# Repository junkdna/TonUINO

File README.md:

# TonUINO
Die DIY Musikbox (nicht nur) für Kinder.

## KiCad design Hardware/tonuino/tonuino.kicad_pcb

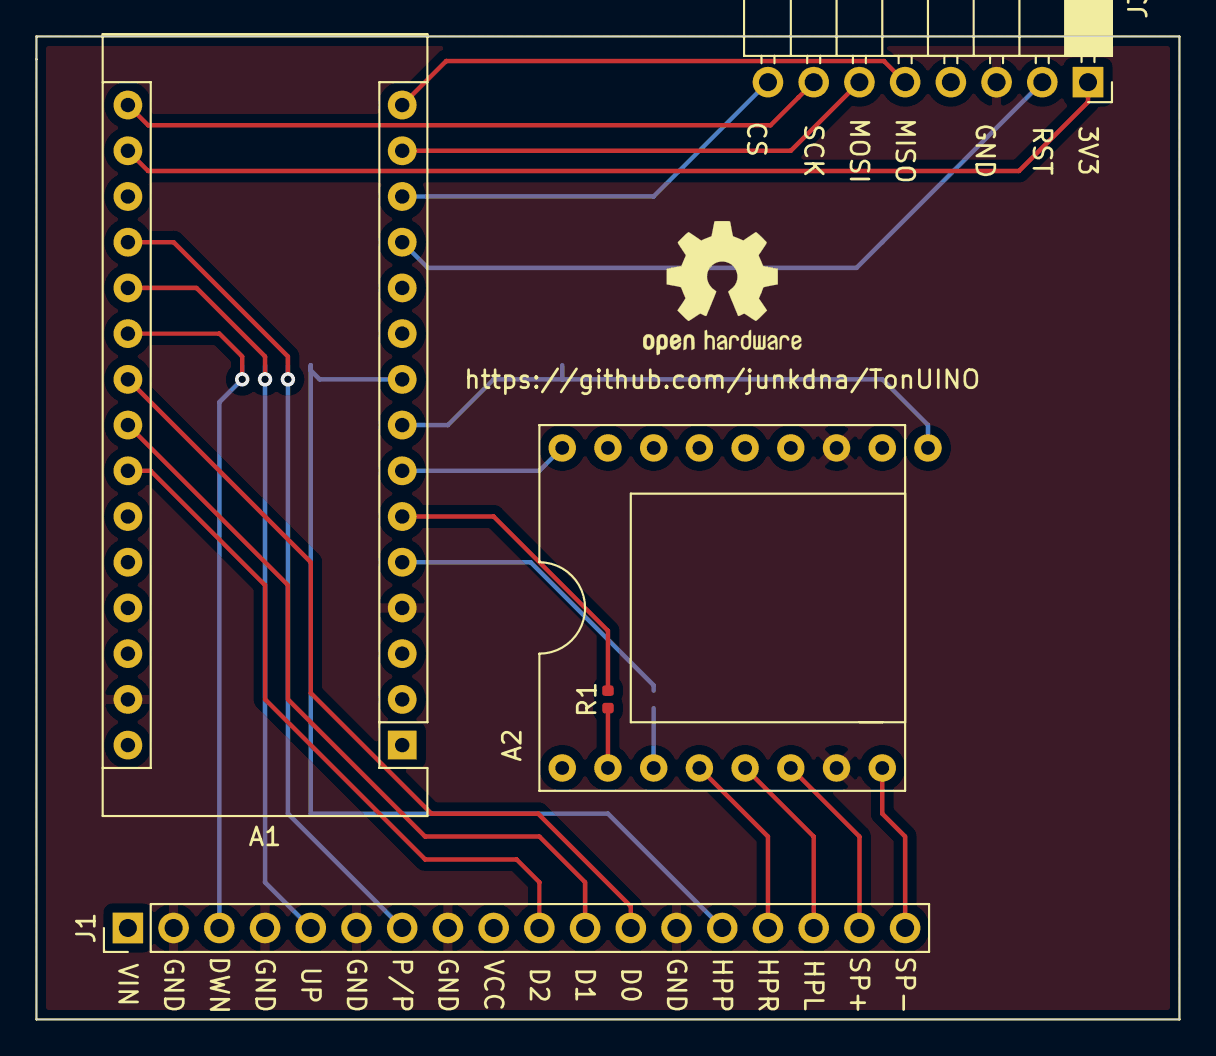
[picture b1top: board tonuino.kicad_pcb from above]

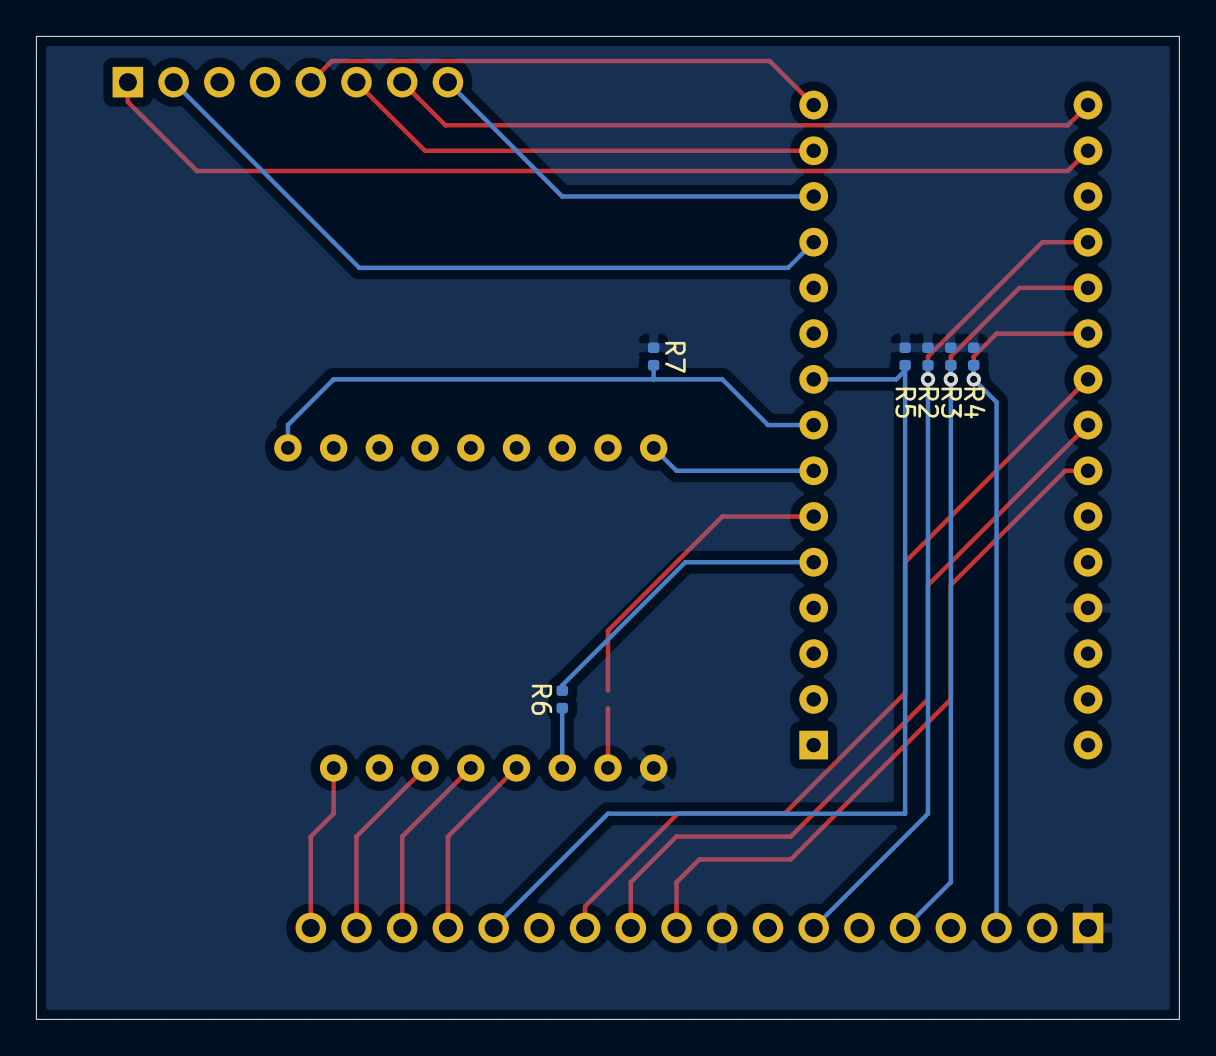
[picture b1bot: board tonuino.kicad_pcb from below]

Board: 2 copper layers, 63.5 x 54.6 mm, 11 parts (6 on the bottom side), 25 nets.

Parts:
A1: Arduino_Nano_v2.x; Arduino_Nano
A2: DFPlayer
J1: Conn_01x18_Female; PinHeader_1x18_P2.54mm_Vertical
J3: Conn_01x08_Female; PinSocket_1x08_P2.54mm_Horizontal
R1: 1k; R_0402_1005Metric
R2, R3, R4, R5, R7: 4k7; R_0402_1005Metric
R6: 0R; R_0402_1005Metric

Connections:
/3V3: A1.17, J3.1
/GND: A1.4, A1.29, A2.7, A2.10, J1.2, J1.4, J1.6, J1.8, J1.13, J3.3
/HEADP_L: A2.5, J1.16
/HEADP_R: A2.4, J1.15
/LED0: A1.22, J1.12
/LED1: A1.23, J1.11
/LED2: A1.24, J1.10
/MISO: A1.15, J3.5
/MOSI: A1.14, J3.6
/RST: A1.12, J3.2
/SCK: A1.16, J3.7
/SPK+: A2.6, J1.17
/SPK-: A2.8, J1.18
/SS: A1.13, J3.8
/VCC: A1.27, A2.1, J1.1, J1.9, R2.1, R3.1, R4.1, R5.1, R7.1
/~DOWN: A1.21, J1.3, R4.2
/~HEADP: A1.9, J1.14, R5.2
/~PAUSE: A1.19, J1.7, R2.2
/~SPK_EN: A1.8, A2.17, R7.2
/~UP: A1.20, J1.5, R3.2
unnamed: A1.5, R6.2
unnamed: A1.6, R1.2
unnamed: A1.7, A2.16
unnamed: A2.2, R1.1
unnamed: A2.3, R6.1

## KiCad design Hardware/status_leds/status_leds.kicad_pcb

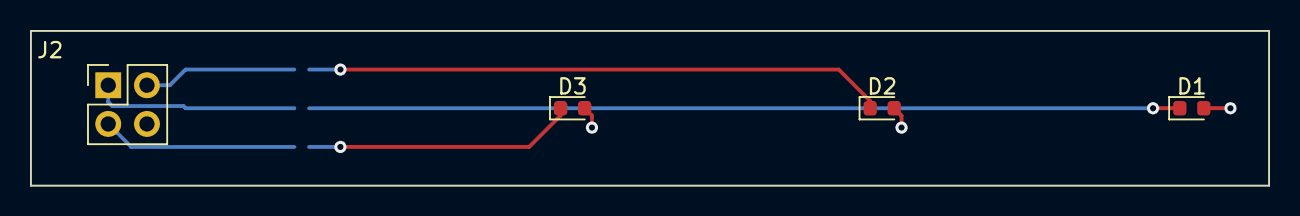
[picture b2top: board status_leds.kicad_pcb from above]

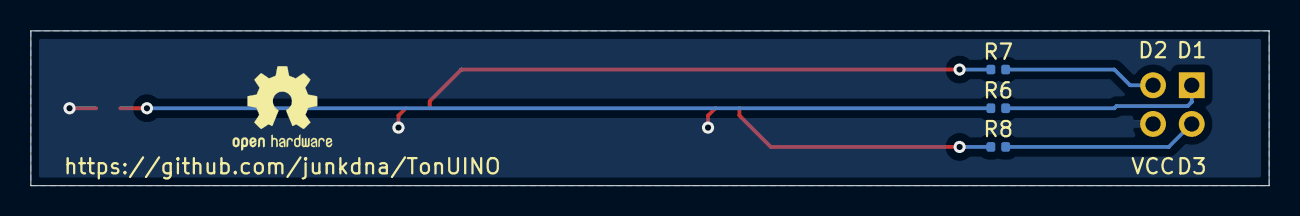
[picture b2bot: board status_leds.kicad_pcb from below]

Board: 2 copper layers, 81.3 x 10.2 mm, 7 parts (3 on the bottom side), 7 nets.

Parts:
D1, D2, D3: LED; LED_0603_1608Metric
J2: Conn_01x04_Female; PinHeader_2x02_P2.54mm_Vertical
R6, R7, R8: 150R; R_0402_1005Metric

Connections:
unnamed: D1.1, R6.1
unnamed: D1.2, D2.2, D3.2, J2.4
unnamed: D2.1, R7.1
unnamed: D3.1, R8.1
unnamed: J2.1, R6.2
unnamed: J2.2, R7.2
unnamed: J2.3, R8.2

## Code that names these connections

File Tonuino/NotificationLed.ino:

/*
 * SPDX-License-Identifier: GPL-3.0-only
 * Copyright 2020 Tillmann Heidsieck <theidsieck@leenox.de>
 */
#include "notification_led.h"

void NotificationLED_3LEDs::loop() {
    uint32_t delta;

    delta = millis() - ms;
    idx %= 3;

    switch (state) {
        case LED_STATE_IDLE:
            if (delta >= 500) {
                digitalWrite(led_pins[idx], 1);
                idx = (idx + 1) % 3;
                digitalWrite(led_pins[idx], 0);
                ms = millis();
            }
            break;
        case LED_STATE_PLAY:
            break;
        case LED_STATE_PAUSE:
            if (delta >= 500) {
                digitalWrite(led_pins[1], idx);
                idx = !idx;
                ms = millis();
            }
            break;
        case LED_STATE_MENU:
            break;
        case LED_STATE_ERROR:
            break;
    }
}

void NotificationLED_3LEDs::update_state(notification_led_state _state) {
    state = _state;
    idx = 0;
    ms = 0;

    /* reset LEDs to off */
    digitalWrite(led_pins[0], 1);
    digitalWrite(led_pins[1], 1);
    digitalWrite(led_pins[2], 1);

    switch (state) {
        case LED_STATE_IDLE:
            digitalWrite(led_pins[0], 0);
            digitalWrite(led_pins[1], 0);
            digitalWrite(led_pins[2], 0);
            break;
        case LED_STATE_PLAY:
            digitalWrite(led_pins[1], 0);
            break;
        case LED_STATE_PAUSE:
            break;
        case LED_STATE_MENU:
            digitalWrite(led_pins[2], 0);
            break;
        case LED_STATE_ERROR:
            digitalWrite(led_pins[0], 0);
            break;
    }
}

NotificationLED_3LEDs::NotificationLED_3LEDs(uint8_t led0, uint8_t led1, uint8_t led2) {
    led_pins[0] = led0;
    led_pins[1] = led1;
    led_pins[2] = led2;
    ms = 0;
    idx = 0;

    pinMode(led_pins[0], OUTPUT);
    pinMode(led_pins[1], OUTPUT);
    pinMode(led_pins[2], OUTPUT);
}

NotificationLED::NotificationLED() {
}

NotificationLED::~NotificationLED() {
}
// vim: ts=4 sw=4 et cindent

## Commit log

2019-12-14 adapt to custom tonuino
2019-12-16 tonuino: indent 4 spaces
2019-12-16 add vim swp files to ignore
2019-12-21 split application code into classes and files
2019-12-22 start implementing the functionality in the new structure
2019-12-26 implement menu (for new card) using new structure
2019-12-26 imported 81d15ffc25344f21b33bbc8fe18b588d05613354 from origin/DEV
    implemented the idea for a better random number generator seed from upstream
2019-12-28 clean up Menu state, improve name
2019-12-28 the rfid code is an example not original code, authorship is important
2019-12-28 clean up RFID reader/writer code
2019-12-28 fix typo in chip id generation
2019-12-28 add toggle for different wirings
2019-12-28 some more cleanup, get rid of compiler warnings
2019-12-28 remove play global tracks states
2019-12-28 rfid: coding style
2019-12-28 rfid: calculate trailer block and sector
2019-12-28 state: make things more consistent
2019-12-28 rfid: style
2019-12-28 rfid: fix card write problem
2019-12-28 state: fix crash after new card
2019-12-28 state: print volume on change
2019-12-28 tonuino: remove mp3 notify debug messages
2019-12-28 buttons: use one bitmap for all events not individual ones
2019-12-28 state: add mp3 event handler for idle state
2019-12-28 state: idle(context) sets the volume not only intialises its internal tracking var
2019-12-28 add some comments noting points for improvement
2019-12-28 state: initial mp3 event handler for album state
2019-12-28 state: remove global_* -> yagni
2019-12-28 state: improve tracking of current track/folder
2019-12-28 state: add play advert wrapper
2019-12-28 state: add play random track from folder helper
2019-12-28 state: fix start() helper
2019-12-28 config: only create new chip_id if id integrity check fails
2019-12-28 config: move to dedicated file
2019-12-28 state: extract button action for vol +/-, next/prev in preperation of config or compile option
2019-12-28 state: harmonise the dfplay_event handler functions basic structure
2019-12-28 state: NewCard: restart and reset tag on initialised tag
2019-12-28 state: harmonise comment in handle_card
2019-12-28 state: implement basic behaviour for states
2019-12-28 setting volume from idle constructor does not work
2019-12-28 state: NewCard: fix track number output
2019-12-28 state: NewCard: save track for single mode in extdata[2] instead of 3
2019-12-28 state: start playing according to card mode
2019-12-28 rfid: fix buffer to struct copy
2019-12-28 state: remove remanents
2019-12-28 rfid: go into correct state in case of errors
2019-12-28 state: AudioBook: fix current_track initialisation
2019-12-28 state: implement prev/next using playFolderTrack
2019-12-28 buttons: ignore release after long_press and only count long_press once
2019-12-28 state: prev/next track numbers are one-indexed
2019-12-28 rfid: clean up check()
2019-12-28 state: do some dirty things to get RadioPlay working
2019-12-29 remove binary files from git
2019-12-29 move schematic to dedicated folder
2019-12-29 move helper script to dedicated folder
2019-12-29 make soundfiles reproducible and match numbers to code
2019-12-29 do not commit mp3 or wave files
2019-12-30 state: improve card handle functions, ignore cards on active playback
2019-12-31 remove non-reproducible schematic pdf
2019-12-31 state: ignore cards in all active states
2019-12-31 state: RadioPlay: fix random play
2019-12-31 state: remove deactivated code
2020-01-03 Merlin/hardware (#1)
    hardware: add baseboard for arduino nano and dfplayer
2020-01-03 state: NewCard: set correct card type for admin cards
2020-01-03 state: skipping 10 modes at a time makes no sense
2020-01-03 state: add simple menu and admin cards to enter it
2020-01-04 make: adapt clean rule
2020-01-04 workflow: test: do not force master branch
2020-01-04 add platformio support
    inspired by
    https://github.com/xfjx/TonUINO/pull/55/
    https://github.com/xfjx/TonUINO/pull/47/
2020-01-04 rfid: fix cppcheck warnings
2020-01-04 ignore build artifacts
2020-01-04 state: fix cppcheck warnings
2020-01-04 readme: add badge
2020-01-04 workflow: test: set working directory
2020-01-04 make: add check target to run c++ check
2020-01-04 add github workflow according to
    https://github.com/xfjx/TonUINO/pull/55
2020-01-04 makefile: remove prepare target
2020-01-04 make: integrate tags generation
2020-01-04 make: update according to referenced pull request
    https://github.com/xfjx/TonUINO/pull/55
2020-01-04 make: fix help
2020-01-04 readme: set correct workflow name
2020-01-05 tools: add gcloud speech synth
2020-01-07 hardware: add additional pull-up for spk_en signal
2020-01-07 hardware: update pcbs
2020-01-07 hardware: prepare split
2020-01-08 Tonuino: add copyright notices to all files
2020-01-08 state: coding style
2020-01-08 state: AlbumRandom: make name consistent
2020-01-08 state: volume: use configured volume steps for inc/dec
2020-01-08 state: clean-up previous state on new card
2020-01-08 make: import changes from upstream
    https://github.com/xfjx/TonUINO/pull/55
2020-01-08 state: NewCard: wrap around selection
2020-01-08 readme: update build badge
2020-01-08 state: get folder track count if not set
2020-01-08 make: remove tags on clean
2020-01-08 state: account for double finished events in dfplay event handler
2020-01-08 make: remove some host dependencies
2020-01-08 state: split up TState.ino into one file per state
    This should improve readability and maintainability.
2020-01-08 make: add some dependencies in order to get a rebuild if required
2020-01-08 state: restore paused playback on play/pause in idle mode
2020-01-08 tonuino: implement configuration reset
2020-01-08 state: play a message on leaving a menu via long press auf play/pause
2020-01-08 rfid: bind card to magic not chip_id
2020-01-08 state: make volume/next/prev configurable
2020-01-08 make: install setuptools and wheel right before platformio
2020-01-08 config: set initial minimal volume to valid value
2020-03-21 config: remove chip id
2020-03-21 hardware: tonuino: fix LED pins, A6/7 are ADC only and wont work as outputs
2020-03-21 player: allow reset of state
2020-03-21 state: idle: play welcome, error on first init, error
2020-03-21 state: idle: track error state
2020-03-21 player/state: add interaction through loop
2020-03-21 player: remove advert on volume change
2020-03-21 player: make player more robust
2020-03-21 player/state: fix regressions
2020-03-21 player: implement random queue instead of pure random mode
2020-03-21 player: fix advert
2020-03-21 button: add define to switch on internal pull-ups for buttons
2020-03-21 tools: create soundfiles: fix skipping
2020-03-21 tools: create soundfiles: put advert and mp3 in the correct folders
2020-03-21 state: fix uninitialised value
2020-03-21 tstate: coding style
2020-03-21 player: play advert on vol up/down
2020-03-21 player: random: do some more rounds of shuffle
2020-03-21 player: get and store global track number
2020-03-21 data/tools: add, sort, modify some messages
2020-03-21 init: do more rounds of random initialisation
2020-03-21 new card: delete any time of card
2020-03-21 mod: LockKeys: return state
2020-03-21 RFID: remove debug code, save 10% flash space
2020-03-21 menu: adjust volume as a preview for volume settings
2020-03-21 player: shuffle: do more rounds for better shuffle
2020-03-21 new card: add modificator card creation
2020-03-21 data: soundfiles: fix/improve text
2020-03-21 player: add some comments explaining the how and what
2020-03-21 eeprom config: fix size and remove unused code
2020-03-21 state/player: propagate errors
2020-03-21 mod: lock keys: play message for lock/unlock
2020-03-21 notification led: add the ability to flash one led on demand
    Flash LED for a short amount of time and turn it off again.
2020-03-21 mp3: improve notification class
2020-03-21 tonuino: remove double init for leds
2020-03-21 state: add support for notification leds
2020-03-21 player: fix error handling behaviour
2020-03-21 state: reset player on state change without restore
2020-03-21 messages: advert shall contain numbers from 1..255
2020-03-21 state: extract player specific code
2020-03-21 tstate: improve stability
2020-03-21 tools: create soundfiles: improve output
2020-03-21 state: add helper to apply modificator cards
2020-03-21 state: add infrastructure for modificatory cards
    Modifications are additive and up to MAX_MODIFICATORS can be active at the same
    time.
2020-03-21 state/player: handle errors
2020-03-21 player: return ok/nok on for some play functions
2020-03-21 hardware: tonuino: add pdfs for easier viewing
2020-03-22 player: adapt to API change of DFPlayer lib
2020-04-02 new card: actually allow to folder number to be played
2020-04-02 player: make interaktions more stable
2020-04-13 setup: delay by generating the random seed
2020-04-13 mod: correctly override/remove existing mods
2020-04-13 state: audiobook: fix init
2020-04-13 state: fix out-of-bounds index due to wrong variable
2020-04-13 mod: improve type definition
2020-04-13 rename .ino to .cpp and handle fallout
2020-04-13 fix various compiler warnings
2020-04-13 remove vim line
2020-04-13 make: check cpp files
2020-04-13 apply format
2020-06-10 tonuino: fix crash after state change in player event
2020-06-19 improve pio configuration
2020-06-19 player: increase timeout
2020-06-19 pio: add compile flags
2020-06-20 player: fix compiler warning
2020-06-20 player: make comment more precise
2020-06-20 player: improve timeouts
2020-06-20 player: improve volume up/down logic
2020-06-20 player: set volume to reasonable volumes on speaker enable/disable
2020-06-20 audio_book: fix saved track number logic
2020-06-20 player: fix compiler warning after deactivating code
2020-06-20 audio_book: fix problems in the constructor
2020-06-20 tonuino: add comment
2020-06-20 player: disable debug output
2020-06-20 player: remove DFPlayer loop, only call loop periodically in loop()
2020-06-20 player: fix: reduce volume on headphone connect
2020-06-20 player: setup: do not reset but stop playback
2020-06-20 player: improve initialisation
2020-06-20 tonuino: print message on reset
2020-06-20 menu: fix copy and paste error
2020-06-20 make: use plattformio instead of arduino
2020-06-20 audio_book: do not try to react to !is_playing
2020-06-21 github: change workflow for platformio integration
2020-06-21 build: remove makefile because we use platformio
2020-06-22 audio_book: do net check for already playing in finished handler
